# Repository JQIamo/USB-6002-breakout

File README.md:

# USB-6002 breakout
BNC/Dsub25 breakout boards for National Instruments USB-6002 DAQ

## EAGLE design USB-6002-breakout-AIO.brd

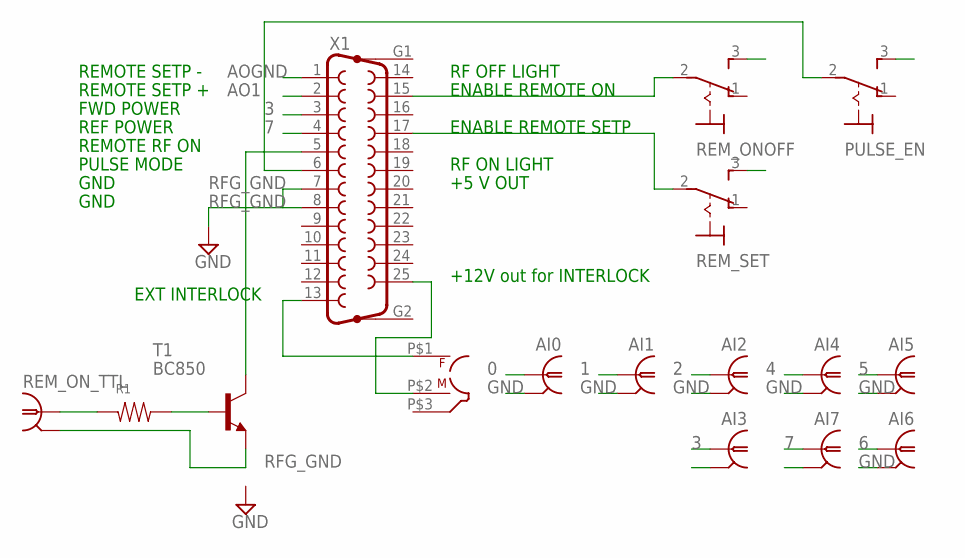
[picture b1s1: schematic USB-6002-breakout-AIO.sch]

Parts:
AI0, AI1, AI2, AI3, AI4, AI5, AI6, AI7: BNC-V
INTERLOCK: TWINAX; TWINAX-V
PULSE_EN: M9040P
R1: RES1206; 1206
REM_ONOFF: M9040P
REM_ON_TTL: BNC-V
REM_SET: M9040P
T1: BC850; SOT23
X1: F25VP

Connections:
0: AI0.1
1: AI1.1
2: AI2.1
3: AI3.1, X1.3
4: AI4.1
5: AI5.1
6: AI6.1
7: AI7.1, X1.4
AO1: X1.2
AOGND: X1.1
GND: AI0.2, AI1.2, AI2.2, AI3.2, AI4.2, AI5.2, AI6.2, AI7.2
unnamed: REM_ONOFF.2, X1.15
unnamed: REM_SET.2, X1.17
unnamed: T1.3 (C), X1.5
unnamed: R1.1, REM_ON_TTL.1
unnamed: R1.2, T1.1 (B)
unnamed: PULSE_EN.2, X1.6
unnamed: INTERLOCK.P$1, X1.13
unnamed: INTERLOCK.P$2, X1.25
RFG_GND: PULSE_EN.3 (S), REM_ONOFF.3 (S), REM_ON_TTL.2, REM_SET.3 (S), T1.2 (E), X1.7, X1.8

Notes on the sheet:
REMOTE SETP -
REMOTE SETP +
FWD POWER
REF POWER
REMOTE RF ON
PULSE MODE
GND
EXT INTERLOCK
+12V out for INTERLOCK
+5 V OUT
RF ON LIGHT
RF OFF LIGHT
ENABLE REMOTE ON
ENABLE REMOTE SETP

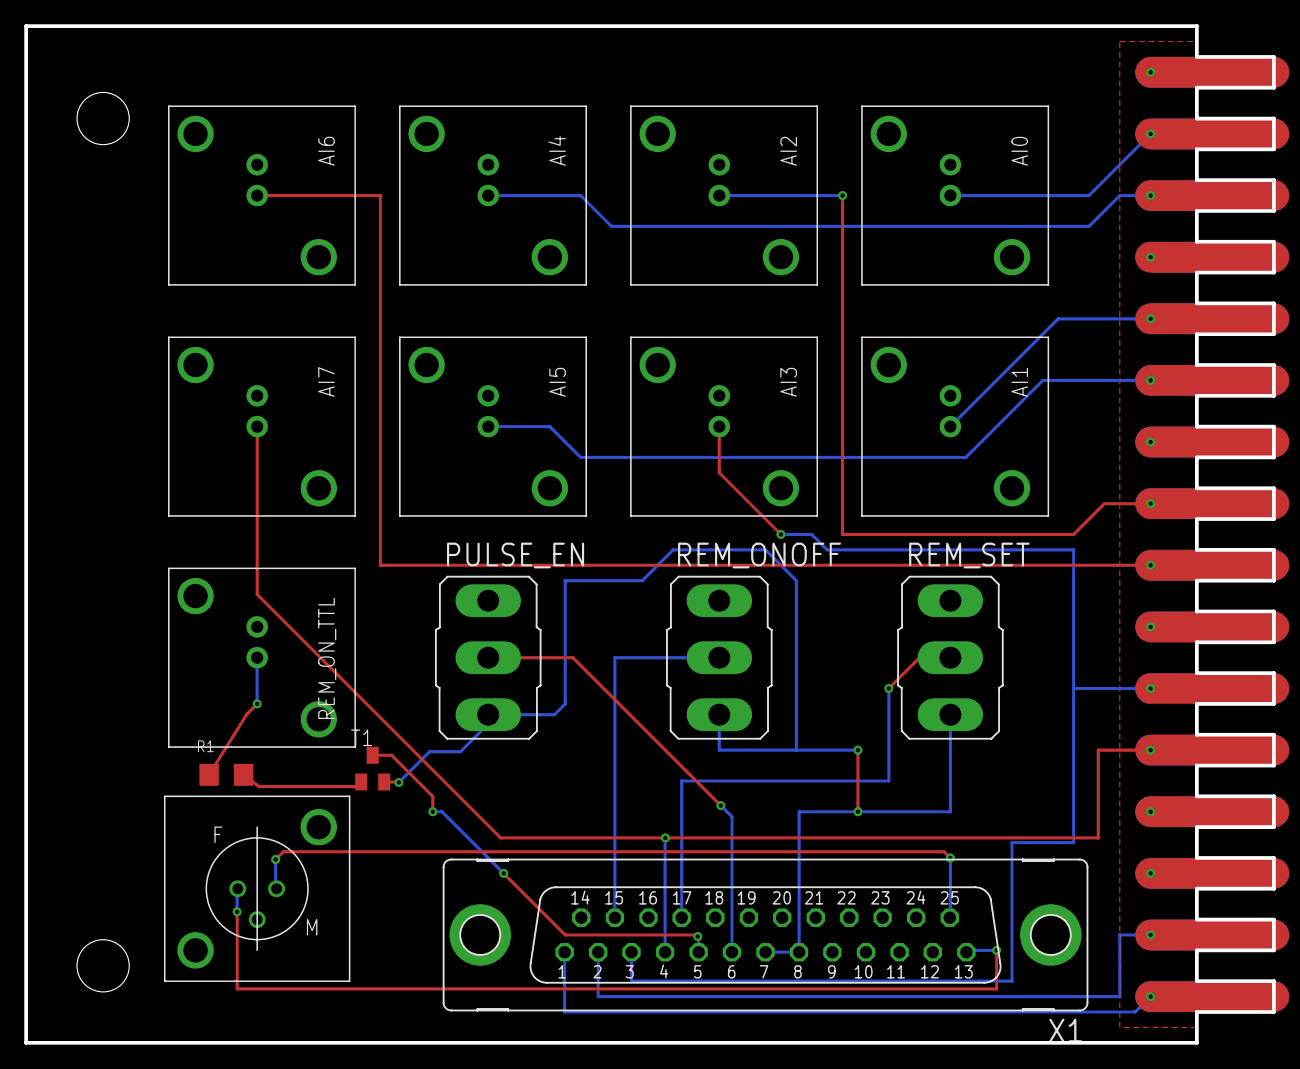
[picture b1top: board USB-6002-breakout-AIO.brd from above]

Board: 2 copper layers, 102.9 x 83.8 mm, 16 parts (0 on the bottom side), 12 nets.

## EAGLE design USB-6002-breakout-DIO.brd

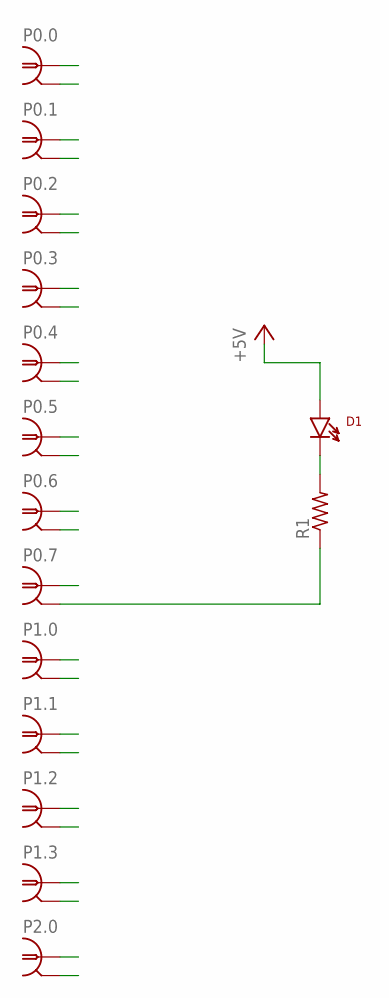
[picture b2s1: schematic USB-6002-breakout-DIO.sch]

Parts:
D1: LED/MINI-IND; HLMP--F0010
P0.0, P0.1, P0.2, P0.3, P0.4, P0.5, P0.6, P0.7, P1.0, P1.1, P1.2, P1.3, P2.0: BNC-V
R1: R-US_M1206; M1206

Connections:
+5V: D1.A
DGND: P0.0.2, P0.1.2, P0.2.2, P0.3.2, P0.4.2, P0.5.2, P0.6.2, P0.7.2, P1.0.2, P1.1.2, P1.2.2, P1.3.2, P2.0.2, R1.1
unnamed: D1.C, R1.2
P0.0: P0.0.1
P0.1: P0.1.1
P0.2: P0.2.1
P0.3: P0.3.1
P0.4: P0.4.1
P0.5: P0.5.1
P0.6: P0.6.1
P0.7: P0.7.1
P1.0: P1.0.1
P1.1: P1.1.1
P1.2: P1.2.1
P1.3: P1.3.1
P2.0: P2.0.1

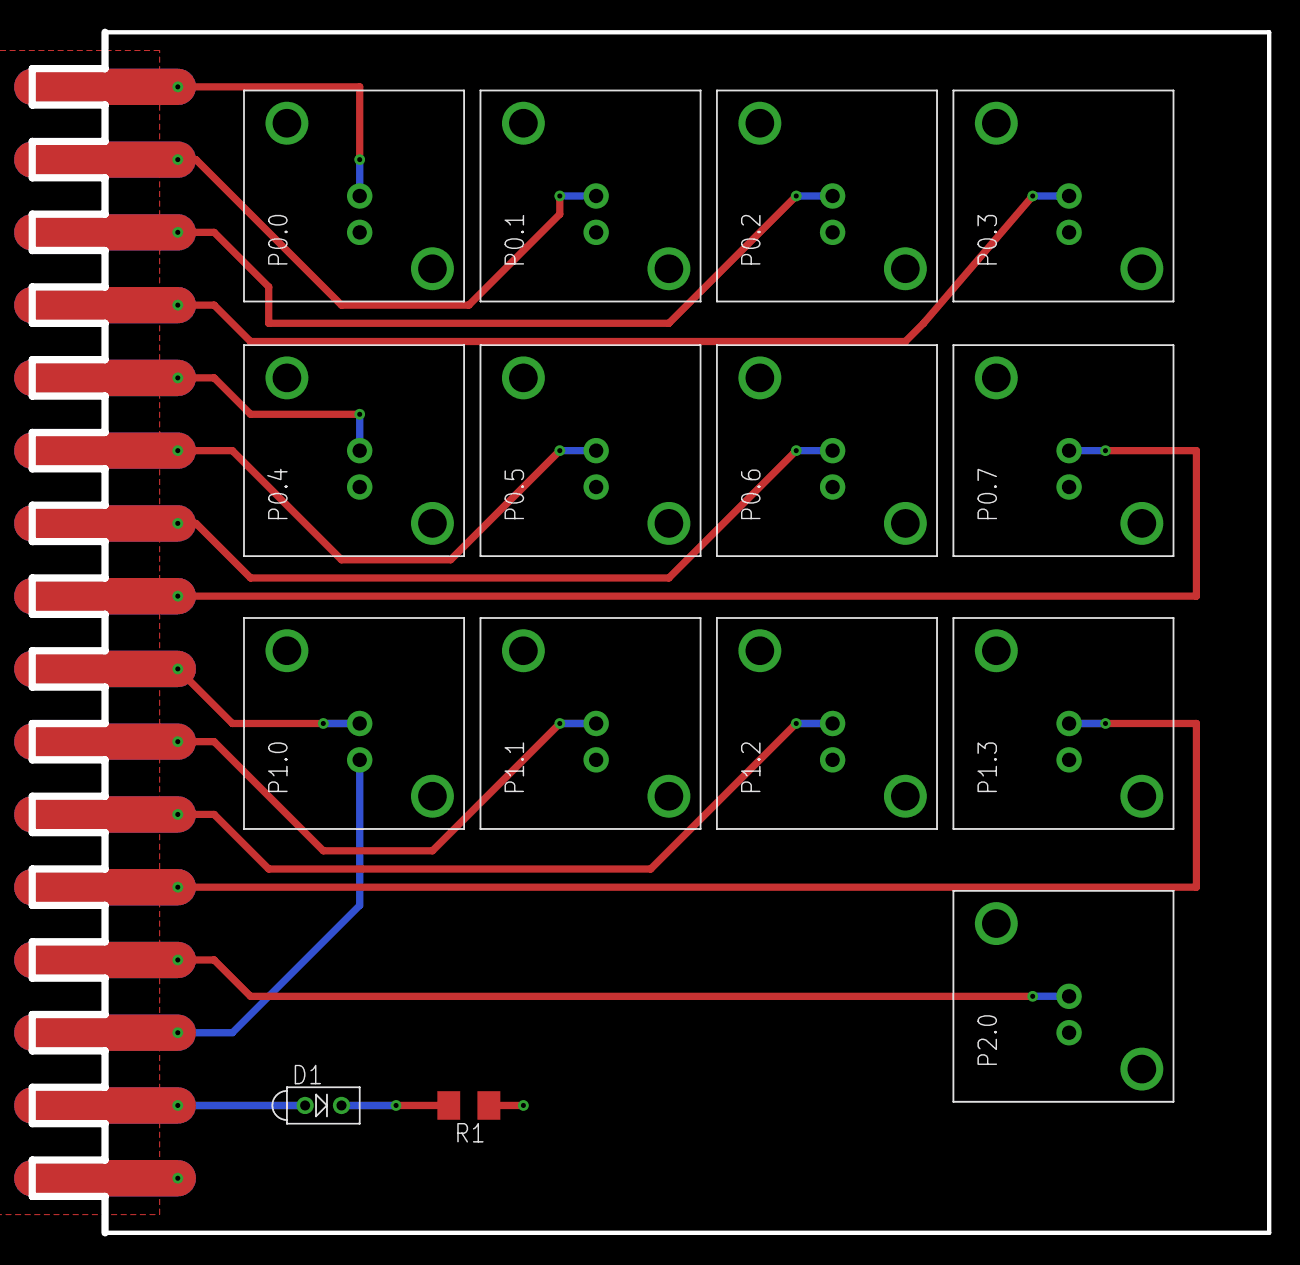
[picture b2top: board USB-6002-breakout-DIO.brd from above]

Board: 2 copper layers, 86.3 x 83.8 mm, 15 parts (0 on the bottom side), 2 nets.

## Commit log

2019-02-08 routing cleanup
2019-02-12 Added AIO breakout board
